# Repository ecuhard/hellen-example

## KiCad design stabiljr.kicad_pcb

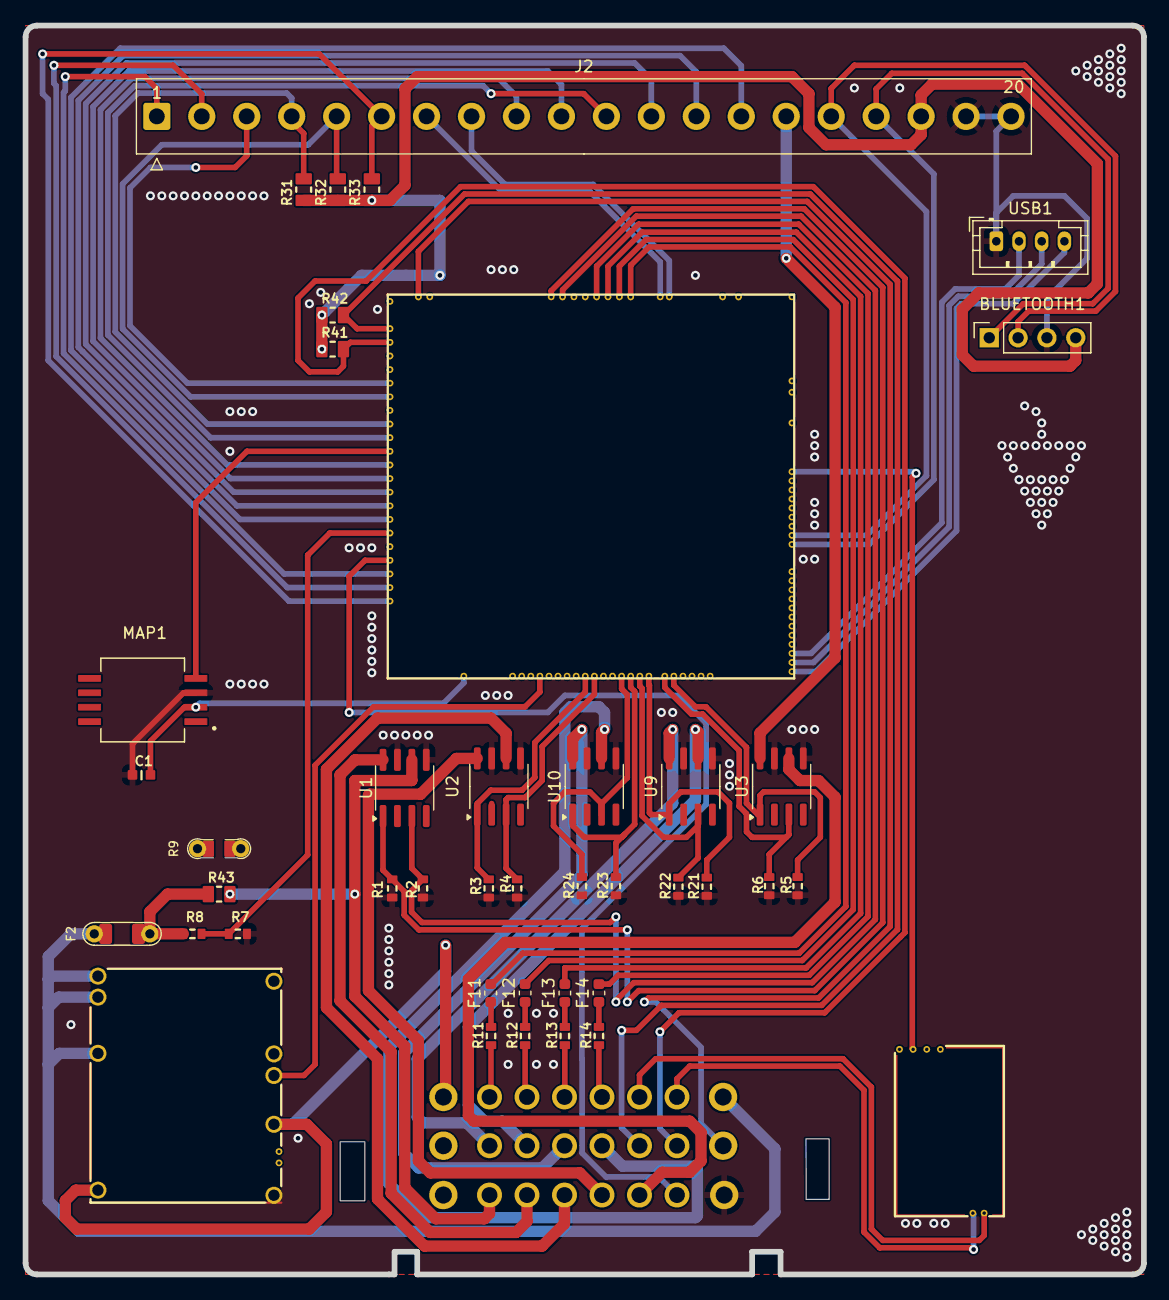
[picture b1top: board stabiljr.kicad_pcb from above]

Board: 4 copper layers, 98.5 x 110.0 mm, 42 parts (0 on the bottom side), 72 nets.

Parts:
BLUETOOTH1: Conn_01x04_Pin; PinSocket_1x04_P2.54mm_Vertical
C1: 100n; C0603
CPU1: Module:mega-mcu100/0.3; mega-mcu100
F2: 12H1500D; PAD-1206-PAD
F11, F12, F13, F14: 50mA; Fuse_0603_1608Metric
J1: Conn_01x24; 24pin
J2: Conn_01x20; TE_2-826576-0_1x20_P3.96mm_Vertical
M1: Module-power_12and5V-0.2; power_12and5V
M4: Module-vr-max9924-0.1; vr-max9924
MAP1: GZP6869D200KPP; MPXH6400A-SSOP8
R1, R2, R3, R4, R5, R6, R21, R22, R23, R24: 4.7k; R0603
R7: 6.8k; R0603
R8: 33k; R0603
R9: Jumper-Pad-Pad; PAD-0805-PAD
R11, R12, R13, R14: 0; R0603
R31, R32, R33: 10k; R0805
R41, R42: 2.7K; R0805
R43: 10K; R0805
U1, U2, U3, U9, U10: VNLD5160TR-E; SOIC-8_3.9x4.9mm_P1.27mm
USB1: Conn_01x04_Pin; JST_PH_B4B-PH-K_1x04_P2.00mm_Vertical

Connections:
+5V: CPU1.N22 (VCC), J1.1, M1.E4 (V5), M1.V4 (5VP)
+5VA: BLUETOOTH1.4, C1.2, CPU1.E1 (V5A_SWITCHABLE), CPU1.W2 (V5A_SWITCHABLE), J2.18, M4.E4 (V5_IN), MAP1.2 (Vs), R31.2, R32.2, R33.2, R41.1, R42.1
+12V: F2.1, R8.2, R43.1
+12V_RAW: F2.2, J1.8, M1.V1 (V12_PERM), M1.V2 (IN_VIGN), M1.V3 (V12_RAW)
/ANALOG 1: CPU1.S18 (IN_TPS_(PA4)), J1.9
/ANALOG 2: CPU1.S19 (IN_PPS_(PA3)), J1.17
/ANALOG 3: CPU1.S11 (IN_O2S_/_CAN_WAKEUP_(PA0)), J2.9
/ANALOG 4: CPU1.S10 (IN_O2S2_(PA1)), J2.10
/ANALOG 5: CPU1.S13 (IN_MAP1_(PC0)), J2.11
/ANALOG 6: CPU1.S9 (IN_AUX1_(PB0)), J2.12
/ANALOG 7: CPU1.S8 (IN_AUX2_(PC4/PE9)), J2.13
/ANALOG 8: CPU1.S7 (IN_AUX3_(PA7)), J2.14
/AUX GROUP 1/IN1: CPU1.W4 (IGN7_(PB9)), R2.1, U1.3 (IN2)
/AUX GROUP 1/IN2: CPU1.W3 (IGN8_(PE6)), R1.1, U1.1 (IN1)
/AUX GROUP 2/IN1: CPU1.E11 (OUT_INJ7_(PD15)), R4.1, U2.3 (IN2)
/AUX GROUP 2/IN2: CPU1.E10 (OUT_INJ8_(PD12)), R3.1, U2.1 (IN1)
/AUX GROUP 3/IN1: CPU1.E18 (OUT_PWM1_(PD13)), R6.1, U3.3 (IN2)
/AUX GROUP 3/IN2: CPU1.E19 (OUT_PWM2_(PC6)), R5.1, U3.1 (IN1)
/BOBIN/IN1: CPU1.W10 (IGN1_(PC13)), F11.2
/BOBIN/IN2: CPU1.W9 (IGN2_(PE5)), F12.2
/BOBIN/IN3: CPU1.W8 (IGN3_(PE4)), F13.2
/BOBIN/IN4: CPU1.W7 (IGN4_(PE3)), F14.2
/BOBİN 1: J1.2, R11.1
/BOBİN 2: J1.3, R12.1
/BOBİN 3: J1.4, R13.1
/BOBİN 4: J1.5, R14.1
/BT_RX: BLUETOOTH1.2, CPU1.N14 (UART2_RX_(PD6)), J2.16
/BT_TX: BLUETOOTH1.1, CPU1.N13 (UART2_TX_(PD5)), J2.17
/CAN1+: CPU1.W11 (CANH), J2.7
/CAN1-: CPU1.W12 (CANL), J2.8
/ENJEKTOR/IN1: CPU1.E17 (OUT_INJ1_(PD3)), R21.2, U9.1 (IN1)
/ENJEKTOR/IN2: CPU1.E16 (OUT_INJ2_(PA9)), R22.2, U9.3 (IN2)
/ENJEKTOR/IN3: CPU1.E15 (OUT_INJ3_(PD11)), R23.2, U10.1 (IN1)
/ENJEKTOR/IN4: CPU1.E14 (OUT_INJ4_(PD10)), R24.2, U10.3 (IN2)
/ENJEKTÖR 1: J1.10, U9.8 (D1)
/ENJEKTÖR 2: J1.11, U9.6 (D2)
/ENJEKTÖR 3: J1.12, U10.8 (D1)
/ENJEKTÖR 4: J1.13, U10.6 (D2)
/INTERNAL_MAP: CPU1.S12 (IN_MAP2_(PC1)), MAP1.4 (Vout)
/IN_BUTTON1: CPU1.S14 (IN_CRANK_(PB1)), J2.4, R31.1
/IN_BUTTON2: CPU1.S16 (IN_CAM_(PA6)), J2.5, R32.1
/IN_BUTTON3: CPU1.S1 (IN_D4_(PE15)), J2.6, R33.1
/IN_CLT: CPU1.S21 (IN_CLT_(PC2)), J1.14, R42.2
/IN_HALL1: CPU1.S4 (IN_D1_(PE12)), J1.23
/IN_HALL2: CPU1.S3 (IN_D2_(PE13)), J2.1
/IN_HALL3: CPU1.S2 (IN_D3_(PE14)), J2.2
/IN_HALL4: CPU1.S17 (IN_VSS_(PE11)), J2.3
/IN_IAT: CPU1.S20 (IN_IAT_(PC3)), J1.15, R41.2
/IN_VMAIN: CPU1.S6 (IN_AUX4_(PC5)), R7.2, R8.1
/PG_5VP: CPU1.N12 (SPI3_MOSI_(PC12)), R9.2
/PWR_EN: CPU1.N20 (OUT_PWR_EN_(PE10)), M1.E5 (EN_5VP)
/USB+: CPU1.N3 (USBP_(PA12)), USB1.2
/USB-: CPU1.N2 (USBM_(PA11)), USB1.3
/VBAT: CPU1.N17 (VBAT), M1.E1 (VBAT)
/VBUS: CPU1.N1 (VBUS), USB1.4
/VIGN: CPU1.E5 (IN_VIGN_(PA5)), M1.E3 (VIGN)
/VR_MAX9924: CPU1.N19 (UART8_TX_(PE1)), M4.E3 (OUT)
/VR_MAX9924+: J1.6, M4.W2 (VR+)
/VR_MAX9924-: J1.7, M4.W1 (VR-)
/ÇIKIŞ 1: J1.18, R43.2, U1.6 (D2)
/ÇIKIŞ 2: J1.19, U1.8 (D1)
/ÇIKIŞ 3: J1.20, U2.6 (D2)
/ÇIKIŞ 4: J1.21, U2.8 (D1)
/ÇIKIŞ 5: J1.22, U3.6 (D2)
/ÇIKIŞ 6: J2.15, U3.8 (D1)
GND: BLUETOOTH1.3, C1.1, CPU1.G (GND), J1.24, J2.19, J2.20, M1.S1 (GND), M4.G (GND), MAP1.3 (GND), R1.2, R2.2, R3.2, R4.2, R5.2, R6.2, R7.1, R21.1, R22.1, R23.1, R24.1, U1.5 (S2), U1.7 (S1), U2.5 (S2), U2.7 (S1), U3.5 (S2), U3.7 (S1), U9.5 (S2), U9.7 (S1), U10.5 (S2), U10.7 (S1), USB1.1
GNDA: CPU1.W1 (GNDA), J1.16
unnamed: F11.1, R11.2
unnamed: F12.1, R12.2
unnamed: F13.1, R13.2
unnamed: F14.1, R14.2
unnamed: M1.E6 (PG_5VP), R9.1

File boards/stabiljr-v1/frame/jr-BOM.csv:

Comment,Designator,Footprint,LCSC Part #
"Conn_01x04_Pin","BLUETOOTH1","PinSocket_1x04_P2.54mm_Vertical","C22438154"
"100n","C1","C0603","C14663"
"Module:mega-mcu100/0.3","CPU1","mega-mcu100",""
"12H1500D","F2","PAD-1206-PAD","C182446"
"50mA","F11","Fuse_0603_1608Metric","C369141"
"50mA","F12","Fuse_0603_1608Metric","C369141"
"50mA","F13","Fuse_0603_1608Metric","C369141"
"50mA","F14","Fuse_0603_1608Metric","C369141"
"Conn_01x24","J1","24pin",""
"Conn_01x20","J2","TE_2-826576-0_1x20_P3.96mm_Vertical",""
"Module:power_12and5V/0.2","M1","power_12and5V",""
"Module:vr-max9924/0.1","M4","vr-max9924",""
"GZP6869D200KPP","MAP1","MPXH6400A-SSOP8","C3038053"
"4.7k","R1","R0603","C23162"
"4.7k","R2","R0603","C23162"
"4.7k","R3","R0603","C23162"
"4.7k","R4","R0603","C23162"
"4.7k","R5","R0603","C23162"
"4.7k","R6","R0603","C23162"
"6.8k","R7","R0603","C23212"
"33k","R8","R0603","C4216"
"Jumper-Pad-Pad","R9","PAD-0805-PAD","C17477"
"0","R11","R0603","C21189"
"0","R12","R0603","C21189"
"0","R13","R0603","C21189"
"0","R14","R0603","C21189"
"4.7k","R21","R0603","C23162"
"4.7k","R22","R0603","C23162"
"4.7k","R23","R0603","C23162"
"4.7k","R24","R0603","C23162"
"10k","R31","R0805","C17414"
"10k","R32","R0805","C17414"
"10k","R33","R0805","C17414"
"2.7K","R41","R0805","ERA6AEB272V"
"2.7K","R42","R0805","ERA6AEB272V"
"10k","R43","R0805","C17414"
"VNLD5160TR-E","U1","SO8","C377942"
"VNLD5160TR-E","U2","SO8","C377942"
"VNLD5160TR-E","U3","SO8","C377942"
"VNLD5160TR-E","U9","SO8","C377942"
"VNLD5160TR-E","U10","SO8","C377942"
"Conn_01x04_Pin","USB1","JST_PH_B4B-PH-K_1x04_P2.00mm_Vertical","C265289"

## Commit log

2025-04-19 test2
2025-04-19 [skip actions] Auto-generated board v2.1
2025-04-19 TEST3
2025-04-19 TEST4
2025-04-19 test5
2025-04-28 GHA says update hellen-one
2025-05-05 GHA says update kicad6-libraries
